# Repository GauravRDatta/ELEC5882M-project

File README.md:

# ELEC5882M-project
This is a readMe file that documents all the source code files and images

1)  Gauss_newton5.m : This code performs an iterative non-linear Gauss-newton algebraic method for 3-D localisation of an initial guesstimate tag location near to its true original location within reasonable accuracy.
Reference paper used: Q. Luo, K. Yang, X. Yan, J. Li, C. Wang, and Z. Zhou, “An Improved Trilateration Positioning Algorithm with Anchor Node Combination and K-Means Clustering,” Sensors, vol. 22, no. 16, p. 6085, Aug. 2022, doi: 10.3390/s22166085.

2) Trilateration_3D.m: This code performs a simple linear algebraic algorithm to determine a position of tag based on ideal conditions using Cramer's rule.

3) Chan2d_tdoa.m : This code performs a non iterative linearised 2-D space TDoA algorithm to estimate an unknown tag's position.
   Reference papers used: Y. T. Chan and K. C. Ho, "A simple and efficient estimator for hyperbolic location," in IEEE Transactions on Signal Processing, vol. 42,       no. 8, pp. 1905-1915, Aug. 1994, doi: 10.1109/78.301830. 
   https://ieeexplore.ieee.org/document/301830
   
   S. H. Olsen, “Radio Tracking of Open Range Sheep Methods for Radio Location in a Sub-GHz Base Station Network,” Department of Electronics and Telecommunications,     Jun. 2014. Accessed: Aug. 01, 2023.[Online]. Available: https://ntnuopen.ntnu.no/ntnu-xmlui/handle/11250/2371123.

5) ADC_plot.m : Plots ADC erros vs ideal characteristics. ADC readings from ADC1Test_readings.txt
6) STM32L476RG_DW3000_code.txt : A C program file that documents all the register address and programming done for a simple transmit case.

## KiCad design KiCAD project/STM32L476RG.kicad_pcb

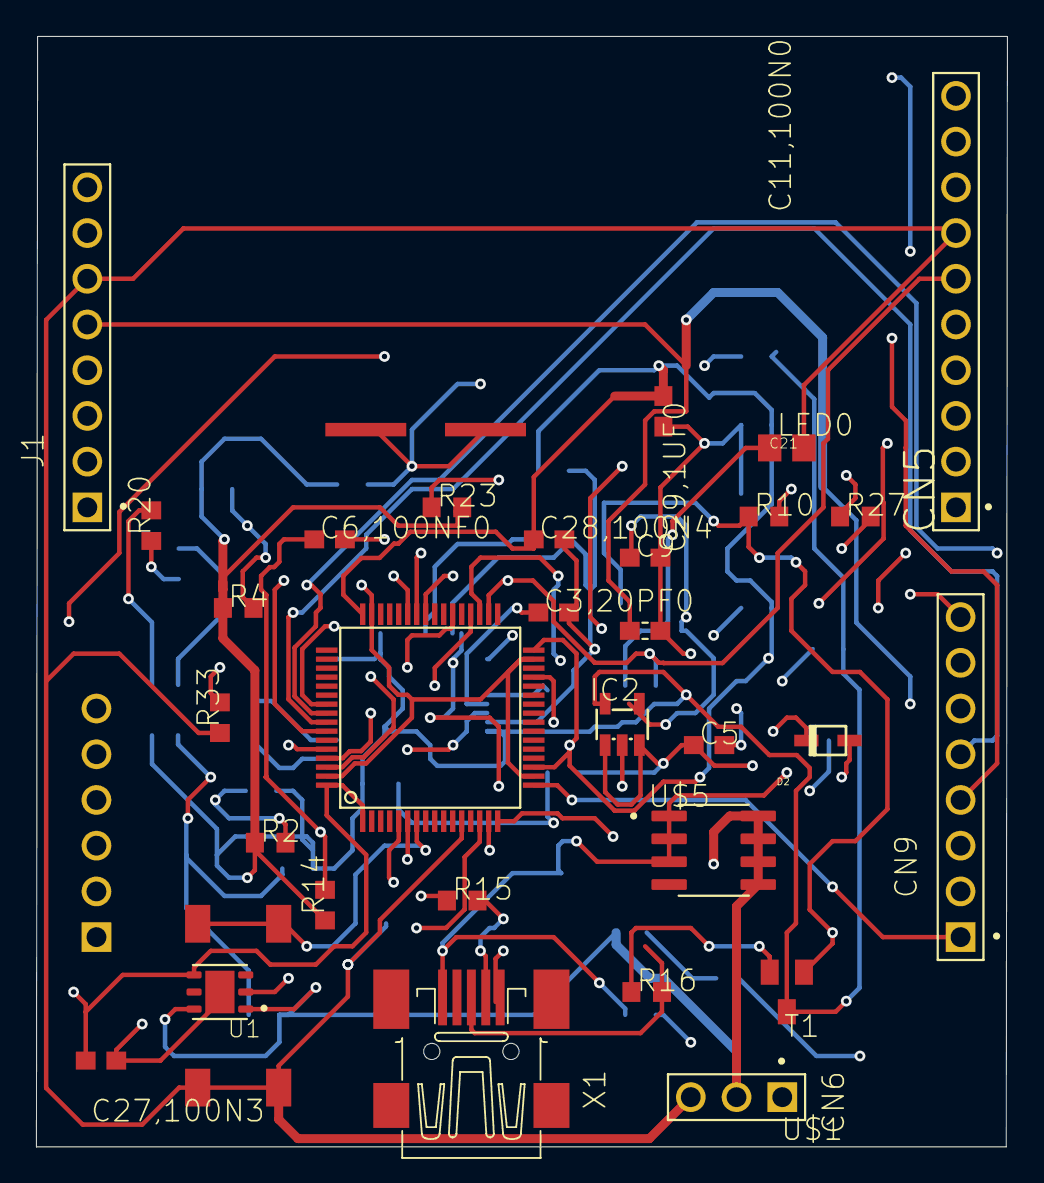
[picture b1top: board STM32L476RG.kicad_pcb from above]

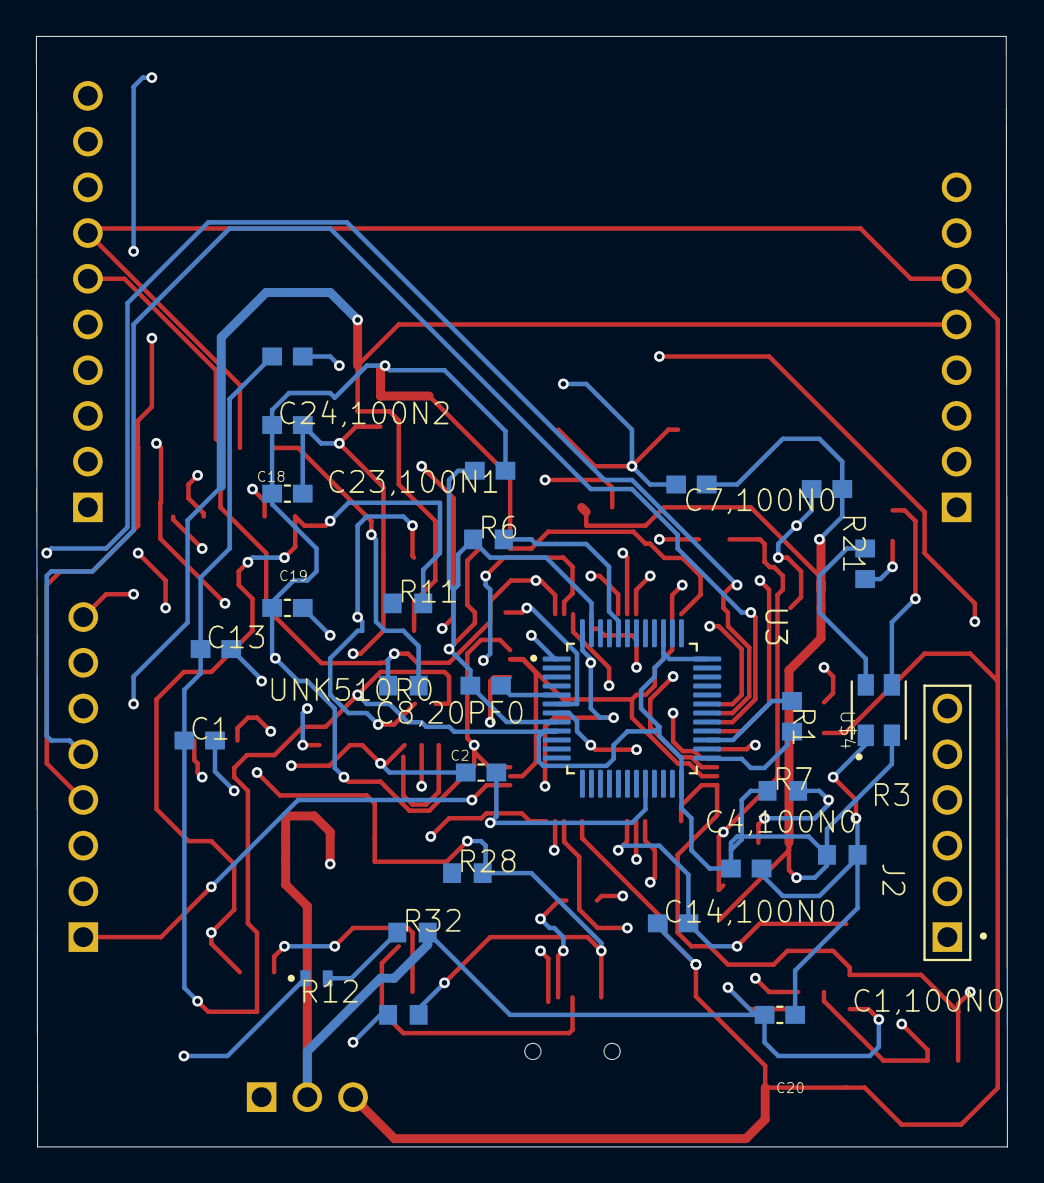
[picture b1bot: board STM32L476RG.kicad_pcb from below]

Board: 4 copper layers, 53.9 x 61.7 mm, 60 parts (28 on the bottom side), 47 nets.

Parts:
C1, C1,100N0, C3,20PF0, C4,100N0, C5, C6,100NF0, C7,100N0, C8,20PF0, C9, C11,100N0, C13, C14,100N0, C23,100N1, C24,100N2, C27,100N3, C28,100N4, C29,1UF0: C0603
C2, C18, C21: CC0603KRX5R8BB105; CAPC1608X90
C19, C20: CC0603KRX7R9BB104; CAPC1608X90
CN5: 61301011121
CN6: 61300311121
CN9: 61300811121
D1: 19-213/R6C-AP1Q2B/3T; LED_19-213_R6C-AP1Q2B_3T
D2: BAT60JFILM; SOD323
IC2: LD398529RM; SOT23-5L
J1: 61300811121
J2: 61300611121
LED0: R0805
R1, R11, R20, R21: 100; R0603
R2, R7: 2.7k; R0603
R3, R4, R23, R27: 4.7k; R0603
R6: R0603
R10: 36k; R0603
R12, R33: 10k; R0603
R14, R15: 100k; R0603
R16: 1.5k; R0603
R28: 4k7; R0603
R32: 1k; R0603
T1: BC850; SOT23
U1: LD39050PU33R; SON95P300X300X100-7N
U3: STM32F103CBT6; QFP50P900X900X160-48N
U$1: STM32L476RCT; LQFP64
U$2: PUSHBUTTON
U$3: 8MHZ_XTAL
U$4: LED_BICOLOR; LED_XZM2CRKM2DGFBB45SCCB
U$5: STS9P3LLH6; SOIC127P600X175-8N
UNK510R0: R0603
X1: MINI-USB-32005-201; 32005-201

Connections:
3V3: CN6.1, U3.1, U3.48
3V3ST_LINK: C1.1, C1,100N0.1, C4,100N0.1, C7,100N0.1, C11,100N0.1, C13.1, IC2.5, R2.1, R3.1, R4.1, R7.1, R14.1, R23.2, T1.3, U3.9, U3.24, U3.36, U3.39, U$4.4
5V: C20.1, C21.1, CN6.2, J1.5, R32.2, U1.1, U1.6, U$5.5, U$5.6, U$5.7, U$5.8
AGND: C14,100N0.1, CN5.7, CN6.3, J1.6, LED0.2, R33.1, U$1.12, U$2.1, U$2.2
E5V: R2.2, R7.2
GND: C1.2, C1,100N0.2, C2.2, C3,20PF0.2, C4,100N0.2, C5.2, C6,100NF0.2, C7,100N0.2, C8,20PF0.2, C9.2, C11,100N0.2, C13.2, C18.2, C19.2, C20.2, C21.2, C23,100N1.2, C24,100N2.2, C27,100N3.2, C28,100N4.2, C29,1UF0.2, D1.1, IC2.2, R3.2, R4.2, R6.1, R10.2, R15.1, R27.2, U1.2, U1.7, U3.8, U3.20, U3.47, U$1.5, U$1.6, U$3.1, U$3.2, U$4.1, X1.5
LED_STLINK: R20.1, R21.1
unnamed: LED0.1, UNK510R0.2
unnamed: R33.2, U$1.60
unnamed: C6,100NF0.1, R14.2, U3.7
unnamed: C3,20PF0.1, U3.6
unnamed: C8,20PF0.1, U3.5
unnamed: R15.2, X1.4
unnamed: R16.1, T1.2
unnamed: R10.1, R11.2, R12.1, T1.1
unnamed: R23.1, R27.1
unnamed: C9.1, IC2.4
unnamed: C2.1, C5.1, D2.C, IC2.1, IC2.3
unnamed: R21.2, U$4.2
unnamed: R20.2, U$4.3
unnamed: D1.2, R32.1
unnamed: R6.2, U3.44
NRST: C14,100N0.2, U$1.7, U$2.3, U$2.4
PA0: J2.1, U$1.14
PA1: J2.2, U$1.15
PA2: CN9.2, U$1.16
PA3: CN9.1, U$1.17
PA8: CN9.8, U$1.41
PA9: CN5.1, U$1.42
PA10: CN9.3, U$1.43
PB3: CN9.4, U$1.55
PB4: CN9.6, U$1.56
PB5: CN9.5, U$1.57
PB6CS/N: CN5.3, U$1.58
PB8: CN5.10, U$1.61
PB9: CN5.9, U$1.62
PB10: CN9.7, U$1.29
PB13SCK: CN5.6, U$1.34, UNK510R0.1
PB14MISO: CN5.5, U$1.35
PB15MOSI: CN5.4, U$1.36
PC7: CN5.2, U$1.38
T_JTMS: R1.1, U3.27
T_SWDIO_IN: R1.2, U3.25
U5V: D2.A, R12.2, R28.2, U$5.1, U$5.2, U$5.3, X1.1
USB_DP: R16.2, X1.3
VDD: C18.1, C19.1, C23,100N1.1, C24,100N2.1, C27,100N3.1, C28,100N4.1, C29,1UF0.1, U1.4, U$1.1, U$1.19, U$1.32, U$1.48, U$1.64
VSS: U$1.18, U$1.31, U$1.47, U$1.63

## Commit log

2023-08-06 Trilateration program
    This program is an introductory program for linear algebra for solving a set of linear equations with a known data point (Transmitter in UWB case) with the help of Cramers rule
2023-08-06 Trilateration 3-D figure
    Cramer's rule program output
2023-08-10 Create UART and ADC outputs
2023-08-10 Add files via upload
    This is the source code for Chan's algorithm. Reference is provided
2023-08-10 Add files via upload
    Gauss-Newton algorithm for 3-D space. Reference is provided.
2023-08-10 Add files via upload
    Code to plot ADC error
2023-08-10 Add files via upload
    KiCAD project file
2023-08-10 Add files via upload
    ADC output via UART
2023-08-10 Add files via upload
    ADC readings original
2023-08-14 Add files via upload
    This is the main .C source code for the microcontroller
2023-08-14 Create README.md
    A README file created
